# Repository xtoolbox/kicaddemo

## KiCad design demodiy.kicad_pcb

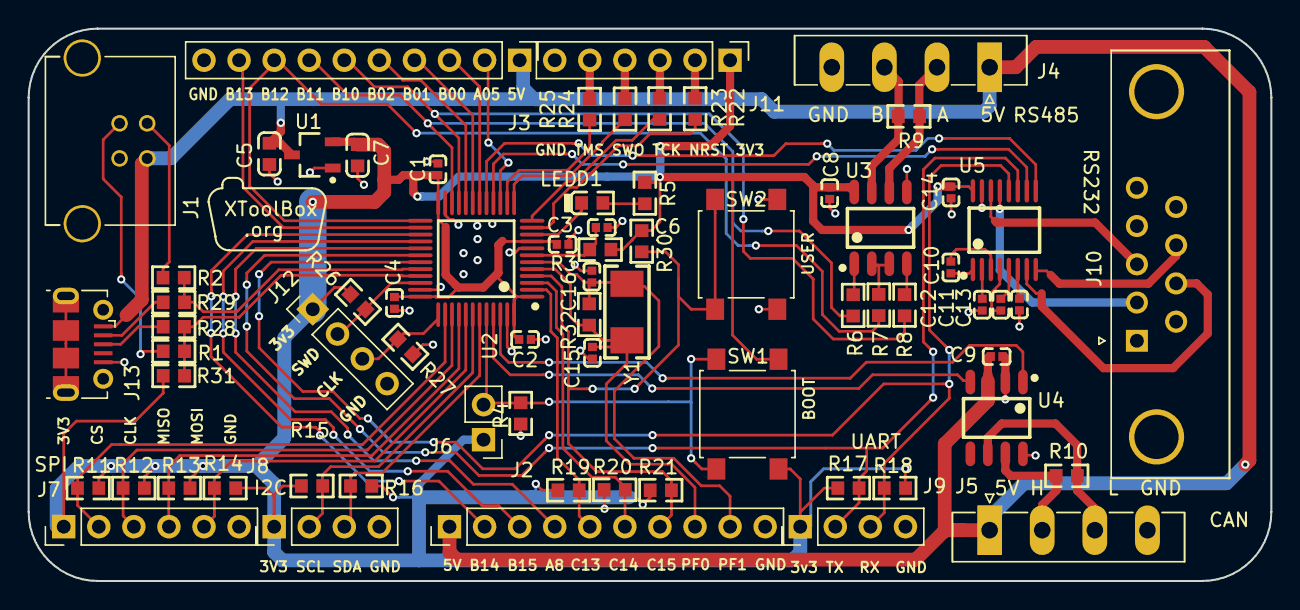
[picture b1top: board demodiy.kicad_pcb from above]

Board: 2 copper layers, 90.0 x 40.0 mm, 70 parts (0 on the bottom side), 68 nets.

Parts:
C1, C2, C3, C4, C6, C8, C9, C10, C11, C12, C13, C14: 0402_100nF__104_10%_16V; 0402_C
C5, C7: 0603_10uF__106_10%_10V; 0603_C
C15, C16: 0402_20pF__200_5%_50V; 0402_C
D1: 0603_蓝灯; 0603_LED_S1
J1: USB_B
J2, J3: Conn_01x10; Pin_Header_Straight_1x10_Pitch2.54mm
J4, J5: Conn_01x04_3.81; PhoenixContact_MC-G_04x3.81mm_Angled
J6: Conn_01x02; Pin_Header_Straight_1x02_Pitch2.54mm
J7, J11: Conn_01x06; Pin_Header_Straight_1x06_Pitch2.54mm
J8, J9, J12: Conn_01x04; Pin_Header_Straight_1x04_Pitch2.54mm
J10: DB9_Female; DSUB-9_Male_Horizontal_Pitch2.77x2.84mm_EdgePinOffset7.70mm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
J13: USB_B_Micro; USB_Micro-B_Molex-105017-0001
R1, R2, R28, R29: 0603_22Ω__22R0_1%; 0603_R
R3, R4, R11, R12, R13, R14, R15, R16, R17, R18, R19, R20, R21, R26, R27, R30: 0603_10KΩ__1002_1%; 0603_R
R5: 0603_1KΩ__1001_1%; 0603_R
R6, R7, R8, R22, R23, R24, R25: 0603_100Ω__1000_1%; 0603_R
R9, R10: 0603_120Ω__1200_1%; 0603_R
R31: 0603_1.5KΩ__1501_1%; 0603_R
R32: 0603_1MΩ__1004_1%; 0603_R
SW1, SW2: SW_Push; SW_SPST_B3S-1000
U1: SOT-23_XC6206P332MR; SOT-23-3L
U2: STM32F103CBT6; LQFP-48_7X7X05P
U3: SP3485EN-L_TR_[C8963]; SOIC-8_150MIL
U4: CAN_TJA1051T_3_[C38695]; SOIC-8_150MIL
U5: SP3232EEY-L_TR_[C13482]; TSSOP-16
Y1: SMD-5032_2P_8MHz_20ppm_20pF; SMD-5032_2P

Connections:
+3V3: C1.1, C2.1, C3.1, C4.1, C7.1, C8.1, C14.1, J6.1, J7.1, J8.1, J9.1, J11.1, J12.1, R3.1, R5.2, R11.1, R12.1, R13.1, R14.1, R15.1, R16.1, R17.1, R18.1, R19.2, R20.2, R21.2, R26.2, R30.2, R31.1, SW1.1, U1.2, U2.1, U2.9, U2.24, U2.36, U2.48, U3.8, U5.16
+5V: C5.1, C9.1, J1.1, J2.1, J3.1, J4.1, J5.1, J13.1, U1.3, U4.3
/485A: J4.2, R9.1, U3.6
/485B: J4.3, R9.2, U3.7
/485_DE: J3.8, R7.1, U2.25
/485_RX: J3.7, R6.1, U2.22
/485_TX: J3.6, R8.1, U2.21
/BOOT0: J6.2, R4.2, SW1.2, U2.44
/CANH: J5.2, R10.1, U4.7
/CANL: J5.3, R10.2, U4.6
/CAN_RX: U2.45, U4.4
/CAN_TX: U2.46, U4.1
/CTS: U2.17, U5.9
/DAC: J3.2, U2.15
/DTR: J2.4, U2.29
/D_CTS: J10.8, U5.8
/D_RD: J10.2, U5.13
/D_RTS: J10.7, U5.7
/D_TD: J10.3, U5.14
/I2C_SCL: J8.2, R15.2, U2.42
/I2C_SDA: J8.3, R16.2, U2.43
/LED: D1.K, U2.10
/NRST: C6.1, R3.2, U2.7
/PB0: J3.3, U2.18
/PB1: J3.4, U2.19
/PB2: J3.5, U2.20
/PB13: J3.9, U2.26
/PB14: J2.2, U2.27
/PB15: J2.3, U2.28
/PC13: J2.5, R19.1, U2.2
/PC14: J2.6, R20.1, U2.3
/PC15: J2.7, R21.1, R30.1, SW2.2, U2.4
/PF0: C15.1, J2.8, R32.1, U2.5, Y1.1
/PF1: C16.1, J2.9, R32.2, U2.6, Y1.2
/RTS: U2.16, U5.10
/RX: J9.3, R18.2, U2.31, U5.12
/SPI_CS: J7.2, R11.2, U2.38
/SPI_MISO: J7.4, R13.2, U2.40
/SPI_MOSI: J7.5, R14.2, U2.41
/SPI_SCK: J7.3, R12.2, U2.39
/SWCLK: J12.3, R27.1, U2.37
/SWDIO: J12.2, R26.1, U2.34
/SWD_NRST: R22.1, U2.11
/SWD_SWO: R24.1, U2.13
/SWD_TCK: R23.1, U2.12
/SWD_TMS: R25.1, U2.14
/TX: J9.2, R17.2, U2.30, U5.11
/USB_D+: R1.2, R28.2, R31.2, U2.33
/USB_D-: R2.2, R29.2, U2.32
GND: C1.2, C2.2, C3.2, C4.2, C5.2, C6.2, C7.2, C8.2, C9.2, C12.2, C13.2, C14.2, C15.2, C16.2, J1.4, J1.5, J2.10, J3.10, J4.4, J5.4, J7.6, J8.4, J9.4, J10.5, J11.6, J12.4, J13.5, J13.6, R4.1, R27.2, SW2.1, U1.1, U2.8, U2.23, U2.35, U2.47, U3.5, U4.2, U4.8, U5.15
unnamed: C10.1, U5.1
unnamed: C10.2, U5.3
unnamed: C11.1, U5.4
unnamed: C11.2, U5.5
unnamed: C12.1, U5.2
unnamed: C13.1, U5.6
unnamed: D1.A, R5.1
unnamed: J1.2, R2.1
unnamed: J1.3, R1.1
unnamed: J11.2, R22.2
unnamed: J11.3, R23.2
unnamed: J11.4, R24.2
unnamed: J11.5, R25.2
unnamed: J13.2, R29.1
unnamed: J13.3, R28.1
unnamed: R6.2, U3.1
unnamed: R7.2, U3.2, U3.3
unnamed: R8.2, U3.4

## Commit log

2018-09-27 add demo project
2018-09-27 Add box to different module
